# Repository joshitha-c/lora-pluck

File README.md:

# LoRa RP2040 Development Board

A custom-designed LoRa development board built in **KiCad**, combining the powerful **Raspberry Pi RP2040** microcontroller with the **Semtech SX1262 LoRa transceiver**. The board is designed for long-range wireless communication, rapid prototyping, IoT applications, and embedded systems development.
This development board is intended for long-range wireless communication and embedded IoT applications. The RP2040 acts as the main controller while the SX1262 provides LoRa connectivity for transmitting and receiving data over long distances.
---

## Features

- RP2040 dual-core ARM Cortex-M0+ microcontroller
- SX1262 LoRa transceiver (Sub-GHz communication)
- USB Type-C interface for programming and power
- External QSPI Flash memory
- 12 MHz crystal for RP2040
- 32 MHz crystal for SX1262
- RF matching network
- Antenna connector
- Reset and Boot buttons
- On-board voltage regulation
- Proper decoupling capacitors for stable operation
- Designed entirely in KiCad

---

## Main Components

| Component | Description |
|------------|-------------|
| RP2040 | Main Microcontroller |
| SX1262 | LoRa Transceiver |
| W25Q Series Flash | External QSPI Flash Memory |
| USB-C Connector | Programming & Power |
| 12 MHz Crystal | RP2040 Clock |
| 32 MHz Crystal | SX1262 Clock |
| RF Matching Network | Impedance Matching |
| Antenna Connector | RF Output |

---

## Future Improvements

- OLED display support
- GPS module
- Battery charging circuit
- Li-ion battery connector
## Tools Used

- KiCad

schematic

pcb

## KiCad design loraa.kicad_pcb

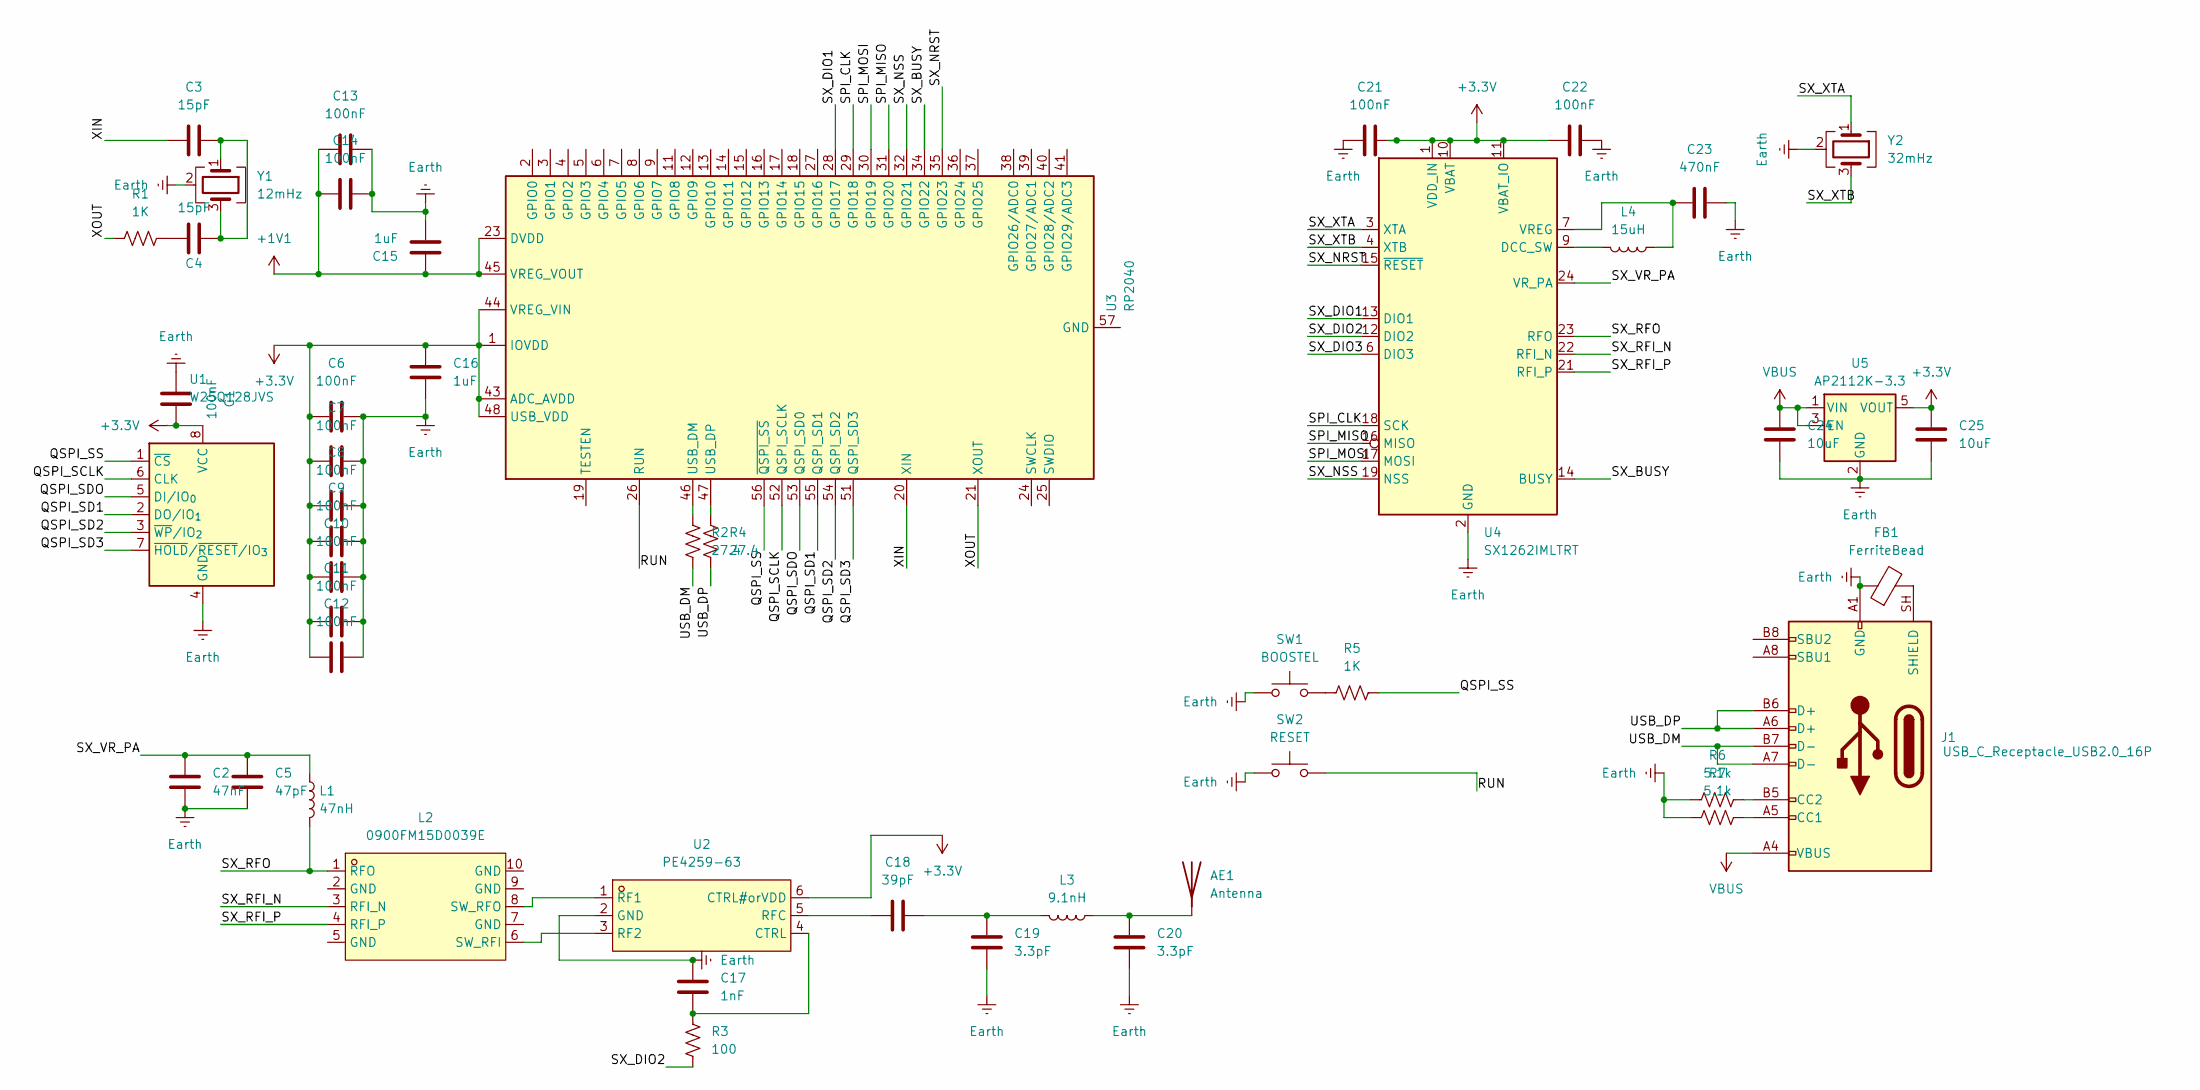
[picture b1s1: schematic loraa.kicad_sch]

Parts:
AE1: Antenna; PinSocket_1x01_P2.54mm_Vertical
C1, C6, C7, C8, C9, C10, C11, C12, C13, C14, C21, C22: 100nF; C_0402_1005Metric
C2: 47nF; C_0402_1005Metric
C3, C4: 15pF; C_0402_1005Metric
C5: 47pF; C_0402_1005Metric
C15, C16: 1uF; C_0402_1005Metric
C17: 1nF; C_0402_1005Metric
C18: 39pF; C_0402_1005Metric
C19, C20: 3.3pF; C_0402_1005Metric
C23: 470nF; C_0402_1005Metric
C24, C25: 10uF; C_0402_1005Metric
FB1: FerriteBead; L_0402_1005Metric
J1: USB_C_Receptacle_USB2.0_16P; USB_C_Receptacle_GCT_USB4105-xx-A_16P_TopMnt_Horizontal
L1: 47nH; L_0402_1005Metric
L2: 0900FM15D0039E; FILTER-SMD_10P-L2.0-W1.3-BL; MPN 0900FM15D0039E; LCSC Part C1513363
L3: 9.1nH; L_0402_1005Metric
L4: 15uH; L_0402_1005Metric
R1, R5: 1K; R_0402_1005Metric
R2, R4: 27.4; R_0402_1005Metric
R3: 100; R_0402_1005Metric
R6, R7: 5.1k; R_0402_1005Metric
SW1: BOOSTEL; SW_Tactile_SPST_NO_Straight_CK_PTS636Sx25SMTRLFS
SW2: RESET; SW_Tactile_SPST_NO_Straight_CK_PTS636Sx25SMTRLFS
U1: W25Q128JVS; SOIC-8_5.3x5.3mm_P1.27mm
U2: PE4259-63; SC-70-6_L2.2-W1.3-P0.65-LS2.1-BL; MPN PE4259-63; LCSC Part C470892
U3: RP2040; QFN-56-1EP_7x7mm_P0.4mm_EP3.2x3.2mm
U4: SX1262IMLTRT; QFN-24-1EP_4x4mm_P0.5mm_EP2.6x2.6mm
U5: AP2112K-3.3; SOT-23-5
Y1: 12mHz; Crystal_SMD_3225-4Pin_3.2x2.5mm
Y2: 32mHz; Crystal_SMD_Abracon_ABM8G-4Pin_3.2x2.5mm

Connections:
+1V1: C13.2, C14.2, C15.2, U3.23 (DVDD), U3.45 (VREG_VOUT), U3.50 (DVDD)
+3.3V: C1.1, C6.2, C7.2, C8.2, C9.2, C10.2, C11.2, C12.2, C16.2, C21.2, C22.1, C25.1, U1.8 (VCC), U2.6 (CTRL#orVDD), U3.1 (IOVDD), U3.10 (IOVDD), U3.22 (IOVDD), U3.33 (IOVDD), U3.42 (IOVDD), U3.43 (ADC_AVDD), U3.44 (VREG_VIN), U3.48 (USB_VDD), U3.49 (IOVDD), U4.1 (VDD_IN), U4.10 (VBAT), U4.11 (VBAT_IO), U5.5 (VOUT)
/QSPI_SCLK: U1.6 (CLK), U3.52 (QSPI_SCLK)
/QSPI_SD1: U1.2 (DO/IO_{1}), U3.55 (QSPI_SD1)
/QSPI_SD2: U1.3 (~WP/IO_{2}), U3.54 (QSPI_SD2)
/QSPI_SD3: U1.7 (~HOLD/~RESET/IO_{3}), U3.51 (QSPI_SD3)
/QSPI_SDO: U1.5 (DI/IO_{0}), U3.53 (QSPI_SD0)
/QSPI_SS: R5.2, U1.1 (~CS), U3.56 (~QSPI_SS)
/RUN: SW2.2, U3.26 (RUN)
/SPI_CLK: U3.29 (GPIO18), U4.18 (SCK)
/SPI_MISO: U3.31 (GPIO20), U4.16 (MISO)
/SPI_MOSI: U3.30 (GPIO19), U4.17 (MOSI)
/SX_BUSY: U3.34 (GPIO22), U4.14 (BUSY)
/SX_DIO1: U3.28 (GPIO17), U4.13 (DIO1)
/SX_DIO2: R3.2, U4.12 (DIO2)
/SX_DIO3: U4.6 (DIO3)
/SX_NRST: U3.35 (GPIO23), U4.15 (~RESET)
/SX_NSS: U3.32 (GPIO21), U4.19 (NSS)
/SX_RFI_N: L2.3 (RFI_N), U4.22 (RFI_N)
/SX_RFI_P: L2.4 (RFI_P), U4.21 (RFI_P)
/SX_RFO: L1.2, L2.1 (RFO), U4.23 (RFO)
/SX_VR_PA: C2.1, C5.1, L1.1, U4.24 (VR_PA)
/SX_XTA: U4.3 (XTA), Y2.1
/SX_XTB: U4.4 (XTB), Y2.3
/USB_DM: J1.A7 (D-), J1.B7 (D-), R2.2
/USB_DP: J1.A6 (D+), J1.B6 (D+), R4.1
/XIN: C3.1, U3.20 (XIN)
/XOUT: R1.1, U3.21 (XOUT)
Earth: C1.2, C2.2, C5.2, C6.1, C7.1, C8.1, C9.1, C10.1, C11.1, C12.1, C13.1, C14.1, C15.1, C16.1, C17.1, C19.2, C20.2, C21.1, C22.2, C23.2, C24.2, C25.2, FB1.1, J1.A1 (GND), J1.A12 (GND), J1.B1 (GND), J1.B12 (GND), R6.2, R7.2, SW1.1, SW2.1, U1.4 (GND), U2.2 (GND), U4.2 (GND), U4.5 (GND), U4.8 (GND), U4.20 (GND), U4.25 (GND), U5.2 (GND), Y1.2 (G), Y1.4 (G), Y2.2 (G), Y2.4 (G)
unnamed: AE1.1 (A_1), C20.1, L3.1
unnamed: C3.2, C4.2, Y1.1, Y1.3
unnamed: C4.1, R1.2
unnamed: C18.1, C19.1, L3.2
unnamed: J1.A5 (CC1), R7.1
unnamed: J1.B5 (CC2), R6.1
unnamed: FB1.2, J1.SH (SHIELD)
unnamed: L2.6 (SW_RFI), U2.3 (RF2)
unnamed: L2.8 (SW_RFO), U2.1 (RF1)
unnamed: R5.1, SW1.2
unnamed: C17.2, R3.1, U2.4 (CTRL)
unnamed: C18.2, U2.5 (RFC)
unnamed: R2.1, U3.46 (USB_DM)
unnamed: R4.2, U3.47 (USB_DP)
unnamed: L4.2, U4.9 (DCC_SW)
unnamed: C23.1, L4.1, U4.7 (VREG)
VBUS: C24.1, J1.A4 (VBUS), J1.A9 (VBUS), J1.B4 (VBUS), J1.B9 (VBUS), U5.1 (VIN), U5.3 (EN)

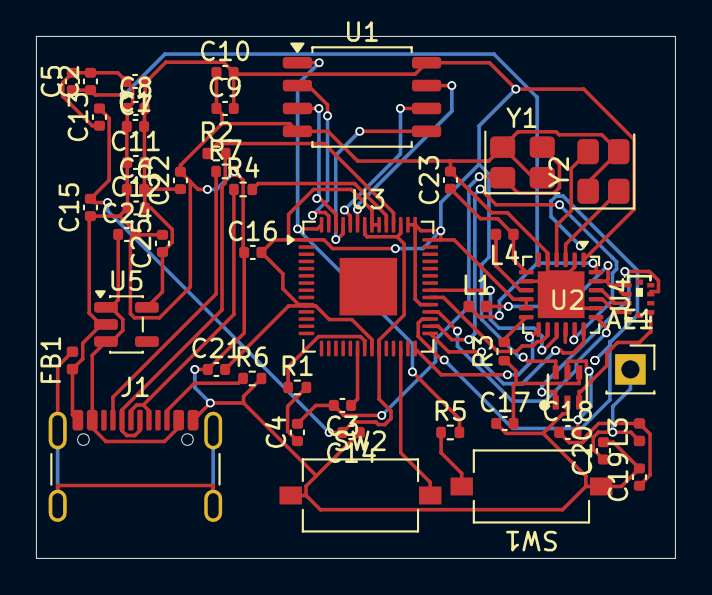
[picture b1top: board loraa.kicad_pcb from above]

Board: 2 copper layers, 35.5 x 29.0 mm, 48 parts (0 on the bottom side), 45 nets.
